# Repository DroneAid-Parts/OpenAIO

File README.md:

# DroneAid OpenAIO

DroneAid OpenAIO is an all-in-one for toothpick-class FPV on 2 to 6 cells: flight controller, 4-in-1 ESC and
ExpressLRS receiver on 25.5 x 25.5 mm mounting, on one PCB. It merges three
boards OpenDrone already makes: OpenFC-Lite-Mini (RP2354A flight controller),
OpenESC-20x20 (AM32 4-in-1) and OpenRX Lite (ELRS receiver). An earlier revision
split it into a Base and a Core hat joined by an LGA; since 2026-10-15 both
are one 8-layer HDI board on the OpenAIO-Whoop stackup.

The KiCad implementation lives in `hardware/`. Use Git for branch state and
manufacturing or test evidence for maturity claims. Layout hand-over:
[research/ROUTING.md](research/ROUTING.md).

## Why

The three-board stack works and OpenDrone already ships all three parts, but on
a toothpick the stack is most of the weight and all of the height. Merging them
removes two connectors, two sets of mounting hardware and a lot of wiring, and
those connectors are where builds fail.

The parts are proven separately, so this is an integration problem rather than
a research one. The only 6S AIO with onboard serial ELRS on the market is
closed and digital-only; an open one with analog OSD and blackbox has a place,
see the market research linked below.

## Specifications

From the design files. Not manufactured yet.

| | |
|---|---|
| Mounting | 25.5 x 25.5 mm, board 35.4 x 35.4 mm |
| Stack | One board: 8-layer HDI 1+6+1, 0.997 mm, 1 oz copper on all layers, ENIG, laser microvias L1-L2 and L7-L8, buried vias L2-L7 (OpenAIO-Whoop stackup). Board rev r3, 2026-10 |
| Input | 2-6S LiPo (6.0-25.2 V), with a low-ESR capacitor of at least 35 V and 220 uF at the battery lead (see Battery lead) |
| Flight controller | RP2354A, BMI270 IMU, DPS368 barometer, analog PIO OSD, microSD blackbox, USB-C |
| ESC | 4x AM32, AT32F421 + NSG2065Q per channel like the OpenESC boards |
| Receiver | ExpressLRS 2.4 GHz, ESP32-C3 + SX1281 |
| Assembly | Chosen per release; see production/. LCSC basic parts preferred |

## Pinout

Measured from `hardware/OpenAIO.kicad_pcb` (pad nets)
and the Betaflight target in `research/review-2026-10/firmware/` (`config.h`,
`PINOUT.md` has the full GPIO map). The silkscreen codes below are the ones
printed next to each pad; port names follow `config.h`.

**Orientation.** Forward is the SH-6 (U12) edge of the Base, battery pads at
the rear. Edge names in the Base table are for the top view with the forward
arrow pointing up (the KiCad view turned 180 degrees). An arrow on the Base top (next to the motor map) and on the Core
bottom (B.Cu copper: no silkscreen may sit in the LGA overlap) points forward. This matches `GYRO_1_ALIGN CW180_DEG`; confirm it in
the configurator Setup tab at bring-up.

### FC pads (the former Core top pads; their place on the one board is not decided yet)

| Pad | Silk | Net | Function |
|---|---|---|---|
| J39 | VTX | `/OSD/VIDEO_OUT` | Analog video out (OSD) to the VTX |
| J38 | CAM | `/OSD/VIDEO_IN` | Analog video in from the camera |
| J30, J37 | 5V | `+5V` | 5 V out |
| J42, J52 | 4V5 (`4.5` at J52) | `+4v5` | 4.5 V rail |
| J34, J35, J40, J43, J50, J53 | GND (`G` where short) | `GND` | Ground |
| J26 | SDA | `/Pads/I2C0.SDA` | I2C0 SDA, GPIO4 (external mag; the onboard DPS368 shares the bus at 0x76) |
| J23 | (legend) SCL | `/Pads/I2C0.SCL` | I2C0 SCL, GPIO5 |
| J44 | TX0 | `/Pads/PIOUART0_TX` | Betaflight UART0 TX, GPIO2 |
| J45 | RX0 | `PU0RX` | Betaflight UART0 RX, GPIO3: SBUS from the air unit (also SH-6 pin 6) |
| J49 | (legend) PTX | `UART0_TX` | Betaflight PIOUART0 TX, GPIO0: MSP DisplayPort (also SH-6 pin 3) |
| J48 | (legend) PRX | `UART0_RX` | Betaflight PIOUART0 RX, GPIO1 (also SH-6 pin 4) |
| J54 | (legend) TX1 | `UART1_TX` | UART1 TX, GPIO6, CRSF to the onboard ELRS (service pad) |
| J55 | RX1 | `UART1_RX` | UART1 RX, GPIO7, CRSF from the onboard ELRS; driven by the ESP32, do not drive it |

The net names are the schematic's; `UART0_TX/RX` on the LGA carry the PIO UART
and `PIOUART0_TX`/`PU0RX` the hardware UART0, because Betaflight cannot run
SBUS on a PIO UART (firmware ISSUES I1).

### Base pads

| Pad | Silk | Net | Function |
|---|---|---|---|
| U24.1 | `+` | `/CSA+` | Battery + (6S), through the current shunt |
| U24.2 | `-` | `GND` | Battery - |
| U24.12-14 | M1 (motor map) | `/1A /1B /1C` | Motor 1, ESC1 (Betaflight MOTOR1, GPIO25): right edge, front half |
| U24.15-17 | M2 | `/2A /2B /2C` | Motor 2, ESC2 (MOTOR2, GPIO24): front edge, right half |
| U24.18-20 | M3 | `/3C /3B /3A` | Motor 3, ESC3 (MOTOR3, GPIO23): rear edge, left half |
| U24.21-23 | M4 | `/4C /4B /4A` | Motor 4, ESC4 (MOTOR4, GPIO22): left edge, rear half |
| J15, J16, J24, J25 | 5V | `+5V` | 5 V for the LED strip, one per corner |
| J17, J18, J27, J28 | GND (bottom) | `GND` | Ground, one per corner |
| J20, J21, J31, J32 | LED (`L` at J20) | `LED_STRIP` | WS2812 data, GPIO8 |
| J41 | (legend) 10V | `+10V` | VTX / air-unit power, always on with a battery (U3 EN is tied to +BATT) |
| J51 | (legend) GND | `GND` | VTX ground |
| U12 | DJI | SH-6 | 1 `+10V`, 2 `GND`, 3 PIOUART0 TX, 4 PIOUART0 RX, 5 `GND`, 6 UART0 RX (SBUS) |
| J33 | BZ+ (bottom) | `+5V` | Buzzer + |
| J29 | BZ- (bottom) | `BUZZER-` | Buzzer - (low-side switched) |
| TP9 | BT0 (bottom) | `/RX/BOOT` | ESP32-C3 boot strap (ELRS flashing) |
| TP31 | (legend) SWD | `SWDIO` | RP2354A SWD data |
| TP32 | (legend) SWC | `SWCLK` | RP2354A SWD clock |
| TP1, TP3, TP4, TP6, TP8 | SD1, SD2, SC2, SC3, SC4 (bottom) | ESC n `PA13`/`PA14` | AM32 SWD of ESC n: SDn = SWDIO (PA13), SCn = SWCLK (PA14) |
| TP2, TP5, TP7 | (legend) SC1, SD3, SD4 | ESC n `PA14`/`PA13` | as above |
| USB1 | none | USB-C | USB (DFU and configurator) |
| JP1 | none | RF | ELRS 2.4 GHz antenna connector |

The motor map (M1-M4 around the forward arrow) on the Base top shows which pad
group belongs to which motor. **Pad legend** for the pads with no room for a
label: Core J23 SCL, J54 TX1, J48 PRX, J49 PTX; Base J41 10V, J51 GND, TP31 SWD,
TP32 SWC, TP2 SC1, TP5 SD3, TP7 SD4. Motor phase letters
are not printed: within each motor group the pads carry phases A, B, C (nets
above); swapping any two reverses the motor, so set direction in AM32 or with
Betaflight's motor direction instead of rewiring.

## Battery lead

- No reverse polarity protection: a reversed battery destroys the board.
- Required: a low-ESR capacitor of at least 35 V (50 V preferred) and 220 uF
  or more at the battery pads. The on-board bank is ceramic only, and a
  hot-plugged 6S pack can ring above the 30 V FETs, the 38 V buck and the 42 V
  current-sense amplifier ([INPUT_RANGE.md](research/review-2026-10/INPUT_RANGE.md)).

## Constraints

- 25.5 x 25.5 mm mounting, the toothpick standard.
- Runs stock firmware: Betaflight on the FC, AM32 per ESC channel, ExpressLRS
  on the receiver. No forks.
- Reuses the manufactured circuits of OpenFC-Lite-Mini, OpenESC-20x20 and
  OpenRX where they fit; parts come from the shared library first.
- Assembly from LCSC parts, extended parts kept to a minimum; assembly house
  chosen per release, see production/.
- Do not start from the three schematics stitched together. That was tried,
  and it produced a board that looked finished and was not (recoverable at the
  `pre-reset-2026-08-13` tag). Start from the requirements.

## Prior art

The three designs this merges, all manufactured and flying:

- [OpenFC-Lite-Mini](https://github.com/OpenDrone-hw/OpenFC-Lite-Mini): the RP2354A flight controller
- [OpenESC-20x20](https://github.com/OpenDrone-hw/OpenESC-20x20): the AM32 4-in-1 power stage
- [OpenRX Lite](https://github.com/OpenDrone-hw/OpenRX-Lite): the ELRS receiver

Research so far, reference rather than decisions:

- [Market research](https://app.notion.com/p/3f5fe06764e1818e9158c512edd58138): competing toothpick and whoop AIOs, June 2026
- [Part alternatives](https://app.notion.com/p/3f5fe06764e1819eade0dc5bfbfdff7c): ESC-stage part alternatives, gate driver and FET options, March 2026
- The stitched design reset in August 2026 is in the git history before #9; reference for the thinking, not a design to continue from.

## Design questions

Resolve these only as part of user-requested design work:

- **Thermal.** Four power stages next to an MCU and a radio on 25.5 mm square,
  with no airflow guarantee. What is the continuous current budget on 1 oz
  copper on all eight layers?
- **RF isolation.** A 2.4 GHz receiver next to four switching power stages.
  Antenna placement, ground plane, shield can or not.

## In the line

What pairs with what, and what is available:
[opendrone.be](https://opendrone.be).

## Contributing

KiCad files cannot be merged, so say what you intend to change before you do,
on [Discord](https://discord.gg/v3sWmTcx3R). How everything works:
[CONTRIBUTING.md](CONTRIBUTING.md).

## License

Hardware licensed under [CERN-OHL-S-2.0](https://ohwr.org/cern_ohl_s_v2.txt),
see [LICENSE](LICENSE).

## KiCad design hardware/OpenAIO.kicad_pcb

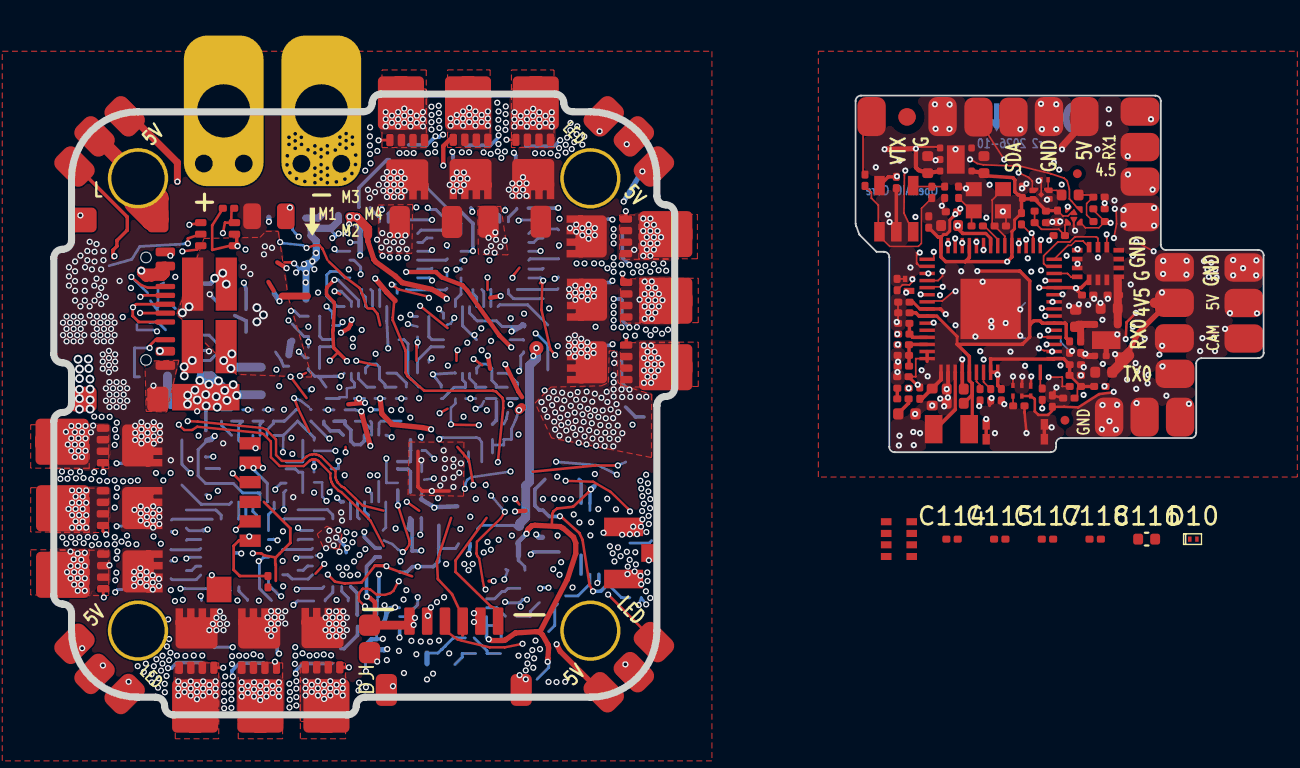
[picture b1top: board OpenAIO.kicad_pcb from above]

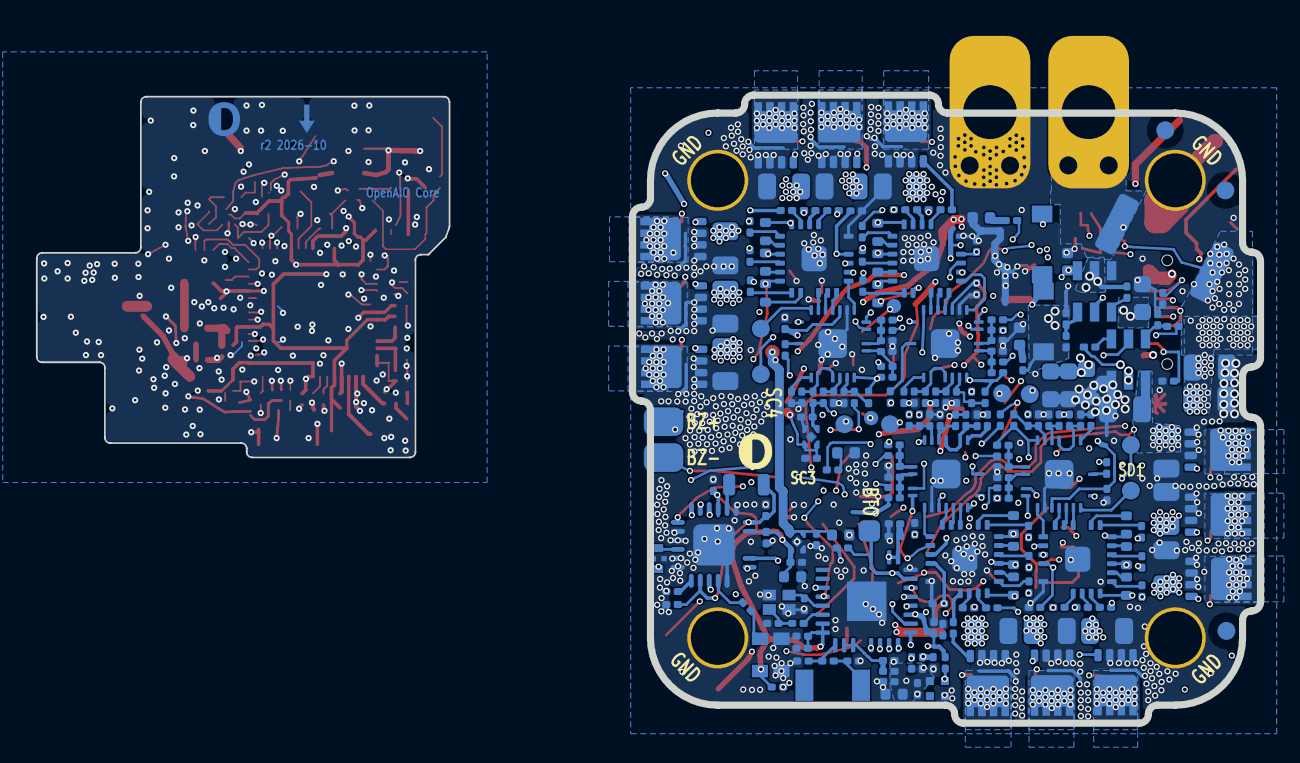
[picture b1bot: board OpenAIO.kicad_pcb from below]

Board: 8 copper layers, 68.2 x 35.0 mm, 362 parts (224 on the bottom side), 239 nets.

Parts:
AE2: 2450AT18A100E; ANT-SMD_L3.2-W1.6
C1, C2, C5, C6, C7, C8, C9, C11, C12, C13, C14, C20, C21, C29, C30, C32, C34, C35, C36, C108, C109, C114, C115, C117, C118: 100n; C_0201_0603Metric
C3, C15, C16, C17, C25, C27: 4.7uF; C_0402_1005Metric
C4, C10: 20p; C_0201_0603Metric
C18, C19, C90, C91, C92, C93, C94, C95, C96, C97, C98, C99, C100, C101, C102, C103: 4.7uF 50v; C_0805_2012Metric
C23, C24, C112, C113: 22uF; C_0603_1608Metric
C26, C28, C33: 1uF; C_0402_1005Metric
C31: 470p; C_0201_0603Metric
C37, C38, C39, C43, C44, C45, C46, C50, C51, C52, C53, C57, C58, C59, C60, C64, C65, C66, C70, C71, C76, C78, C79, C104: 100nF; C_0201_0603Metric
C40, C41, C42, C47, C48, C49, C54, C55, C56, C61, C62, C63: 100nF; C_0402_WIDE
C67, C73, C80: 10nF; C_0201_0603Metric
C68: 470nF; C_0201_0603Metric
C69: 1nF; C_0201_0603Metric
C72, C74: 15pF; C_0201_0603Metric
C75, C82, C88: 10uF; C_0402_1005Metric
C77, C81, C83, C84, C85, C86, C110, C111: 1uF; C_0201_0603Metric
C87, C89: 1.2pF; C_0201_0603Metric
C105, C106: 4.7uF 50v; C_1206_3216Metric
C107, C116: 100nF; C_0402_1005Metric
Card1: TF-021B-H265; TF-SMD_TF-021B-H265
D1: LED_1_Blue; LED_0402_1005Metric
D2, D3: DSK24; SOD-123_L2.8-W1.8-LS3.7-RD
D4, D5, D6, D7: LED_1_Green; LED_0402_1005Metric
D8, D10: SDM02U30LP3-7B; X3-DFN0603-2_L0.6-W0.3-RD
D9: XL-1010RGBC-WS2812B; LED-SMD_4P-L1.0-W1.0-TL_XL-1010RGBC-WS2812B
FID1, FID2, FID3, FID4: Fiducial_1mm_Mask2mm
FID5, FID6: Fiducial_1mm_Mask2mm; Fiducial_0.5mm_Mask1mm
FL1: 2450FM07D0034T; FILTER-SMD_4P-L1.0-W0.5-L
J15, J16, J24, J25, J30, J37: 5V; small_pad
J17, J18, J27, J28, J34, J35, J40, J43, J50, J53: GND; small_pad
J20, J21, J31, J32: LED; small_pad
J23: SCL; small_pad
J26: SDA; small_pad
J29: BUZ-; small_pad
J33: BUZ+; small_pad
J38: CAM; small_pad
J39: VTX; small_pad
J41: 10V; SolderPad_1.2x1.2mm
J42, J52: 4V5; small_pad
J44: PIO_TX0; small_pad
J45: PIO_RX0; small_pad
J48: RX0; small_pad
J49: TX0; small_pad
J51: GND; SolderPad_1.2x1.2mm
J54: TX1; small_pad
J55: RX1; small_pad
JP1: U.FL-R-SMT-1(80); RF-SMD_FRF05002-JSS103M
L1: AOTA-B201610S3R3-101-T; IND-SMD_L2.0-W1.6_AOTA-B201610S3R3-101-T
L2, L3: XRTC303020D4R7MBCA; IND-SMD_L3.0-W3.0_AFE303020S
L4: 15uH; L_0805_2012Metric
L5: 24nH; L_0201_0603Metric
L6: 2.0nH; L_0201_0603Metric
L7: 2.5nH; L_0201_0603Metric
OSC1: OW7EL89CENUNFAYLC-52M; OSC-SMD_4P-L2.0-W1.6-BL_TXC_7Z
Q1: AP1606; DFN-3L_L1.0-W0.6-P0.65-BR
Q3, Q4, Q5, Q6, Q7, Q8, Q9, Q10, Q11, Q12, Q13, Q14, Q15, Q16, Q17, Q18, Q19, Q20, Q21, Q22, Q23, Q24, Q25, Q26: DOY180N03T; DOY180N03T_TDFN3333-8
R1, R13, R17, R19: 100k; R_0201_0603Metric
R2, R25, R34, R37, R38, R45, R47, R48, R50, R51, R53, R56, R57, R64, R66, R67, R69, R70, R72, R75, R76, R83, R85, R86, R88, R89, R91, R94, R95, R102, R104, R105, R107, R108, R110, R111, R112, R113, R114: 10k; R_0201_0603Metric
R3, R4, R11, R12: 5.1k; R_0201_0603Metric
R5, R6, R7, R46, R49, R52, R65, R68, R71, R84, R87, R90, R103, R106, R109: 1k; R_0201_0603Metric
R8, R9, R10: 30R; R_0201_0603Metric
R15, R16, R26, R33: 75R; R_0201_0603Metric
R18, R23: 6.49k; R_0201_0603Metric
R20: 13.7k; R_0201_0603Metric
R21: 7.5k; R_0201_0603Metric
R22: 2.4k; R_0201_0603Metric
R24, R31, R32: 510R; R_0201_0603Metric
R27: 3.9k; R_0201_0603Metric
R28: 12k; R_0201_0603Metric
R29: 1.4k; R_0201_0603Metric
R30: 680R; R_0201_0603Metric
R35, R36, R41, R42, R43, R44, R54, R55, R60, R61, R62, R63, R73, R74, R79, R80, R81, R82, R92, R93, R98, R99, R100, R101: 15R; R_0201_0603Metric
R39, R58, R77, R96: 220R; R_0201_0603Metric
R40, R59, R78, R97: 10R; R_0201_0603Metric
R115: 200R; R_0201_0603Metric
Rsense2: 0.2mR; R_2512_6332Metric
TP1, TP2, TP3, TP4, TP5, TP6, TP7, TP8: TestPoint; TestPoint_Pad_D1.0mm
TP9: BOOT; SolderPad_1.2x2.0mm
TP31: SWDIO; TestPoint_Pad_D0.8mm
TP32: SWCLK; TestPoint_Pad_D0.8mm
U1: TS2306A 240GF MSM 9_C2976675; SW-SMD_4P-L3.0-W2.0-P0.85-LS3.5
U2: RP2354A; QFN-60_L7.0-W7.0-P0.40-TL-EP3.4
U3, U4: LMR51430YFDDCR; SOT-23-6_L2.9-W1.6-P0.95-LS2.9-BL
U6: LP5912-1.8DRVR; WSON-6-1EP_2x2mm_P0.65mm_EP1x1.6mm_ThermalVias
U7: LP5912-3.3DRVR; WSON-6-1EP_2x2mm_P0.65mm_EP1x1.6mm
U8: BMI270; LGA-14_L3.0-W2.5-P0.50-BR
U9: SN74LVC1G3157DTBR; X2SON-6_L1.0-W0.8-BL
U10: COS8051SOT; SOT-23-5_L3.0-W1.7-P0.95-LS2.8-BR
U11: TLV7031DPWR; X2SON-4_L0.8-W0.8-P0.48-TL-A
U12: SM06B-SRSS-TB(LF)(SN); CONN-SMD_SM06B-SRSS-TB-LF-SN
U13, U15, U17, U19: AT32F421G8U7; QFN-28_L4.0-W4.0-P0.40-TL-EP2.4
U14, U16, U18, U20: NSG2065Q; QFN-24_L4.0-W4.0-P0.50-TL-EP2.8
U21: SX1281IMLTRT; QFN-24_L4.0-W4.0-P0.50-TL-EP2.6
U22: ESP32-C3FH4; QFN-32-1EP_5x5mm_P0.5mm_EP3.7x3.7mm
U23, U27: TLV75533PDQNR; X2SON-4_L1.0-W1.0-P0.65-TL-EP
U24: AIO_outline
U25: INA186A3IDCKR; SOT-363_SC-70-6
U26: TXU0101DRYR; SON-6_L1.5-W1.0-P0.50-TL
U28: DPS368XTSA1; LGA-8_L2.5-W2.0-P0.65-TR_DPS368
USB1: TYPE-C 16P QTWT; USB-TYPE-C-SMD_TYPE-C-16P-QTWT
X1: XTM25012000JT00351001; CRYSTAL-SMD_4P-L2.5-W2.0-BL-A
X2: CJ17-400001010B20; CRYSTAL-SMD_4P-L1.6-W1.2-BL

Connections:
+1.1V: C1.1, C3.1, C5.1, C16.1, L1.1, U2.6 (DVDD), U2.23 (DVDD), U2.39 (DVDD), U2.50 (VREG_FB)
+1.8V_GYRO: C27.1, C29.1, U6.1 (OUT), U8.8 (Vdd)
+3.3V: C6.1, C7.1, C8.1, C11.1, C12.1, C13.1, C14.1, C15.1, C28.1, C30.1, C32.1, C34.1, C35.1, C36.1, C108.1, C114.1, C115.1, C117.1, C118.1, Card1.4 (VDD), R10.1, R11.1, R12.1, R25.2, R28.2, R34.1, U2.1 (IOVDD), U2.11 (IOVDD), U2.20 (IOVDD), U2.26 (RUN), U2.30 (IOVDD), U2.38 (IOVDD), U2.44 (ADC_AVDD), U2.45 (IOVDD), U2.49 (VREG_VIN), U2.53 (USB_OTP_VDD), U2.54 (QSPI_IOVDD), U7.1 (OUT), U8.2 (SDx/AH1/Qvar1), U8.3 (SCx/AH2/Qvar2), U8.5 (Vdd_IO), U9.5 (VCC), U10.5 (+VS), U11.2 (VCC), U26.1 (VCCA), U28.2 (CSB), U28.6 (VDDIO), U28.8 (VDD)
+3V3: C65.1, C66.1, C70.1, C71.1, C75.1, C76.1, C78.1, C79.1, C80.1, C81.1, C83.1, C86.1, C88.1, C104.1, L6.2, OSC1.4 (VDD), R24.1, R111.1, R112.1, R113.1, R114.2, U21.11 (VBAT_IO), U21.15 (VBAT), U22.11 (VDD3P3_RTC), U22.17 (VDD3P3_CPU), U22.18 (VDD_SPI), U22.31 (VDDA), U22.32 (VDDA), U23.1 (OUT), U25.3 (VS)
+3V3_ESC: C39.1, C46.1, C53.1, C60.1, C111.1, R37.2, R40.2, R56.2, R59.2, R75.2, R78.2, R94.2, R97.2, U13.17 (VDD), U15.17 (VDD), U17.17 (VDD), U19.17 (VDD), U27.1 (OUT)
+4v5: C25.1, C26.1, C82.1, C85.1, D2.1 (K), D3.1 (K), D9.2 (VDD), J42.1 (Pin_1_1), J52.1 (Pin_1_1), R23.1, U6.4 (EN), U6.6 (IN), U7.4 (EN), U7.6 (IN), U23.3 (EN), U23.4 (IN)
+5V: C24.1, C109.1, C110.1, D2.2 (A), D10.1 (C), J15.1 (Pin_1_1), J16.1 (Pin_1_1), J24.1 (Pin_1_1), J25.1 (Pin_1_1), J30.1 (Pin_1_1), J33.1 (Pin_1_1), J37.1 (Pin_1_1), L3.2, R19.2, R22.1, U26.5 (OE), U26.6 (VCCB), U27.3 (EN), U27.4 (IN)
+5V_USB: D3.2 (A), USB1.A4 (VBUS), USB1.A9 (VBUS)
+10V: C23.1, C43.1, C50.1, C57.1, C64.1, C112.1, C113.1, J41.1 (Pin_1_1), L2.2, R17.2, R21.1, U12.1, U14.4 (VCC), U16.4 (VCC), U18.4 (VCC), U20.4 (VCC)
+BATT: C18.1, C19.1, C90.1, C91.1, C92.1, C93.1, C94.1, C95.1, C96.1, C97.1, C98.1, C99.1, C100.1, C101.1, C102.1, C103.1, C105.1, C106.1, C107.1, C116.1, Q3.3 (D), Q5.3 (D), Q7.3 (D), Q9.3 (D), Q11.3 (D), Q13.3 (D), Q15.3 (D), Q17.3 (D), Q19.3 (D), Q21.3 (D), Q23.3 (D), Q25.3 (D), R1.2, Rsense2.2, U3.3 (VIN), U3.5 (EN), U4.3 (VIN), U4.5 (EN), U25.5 (-IN)
/1A: C40.1, Q3.1 (S), Q4.3 (D), R47.1, U14.18 (VS1), U24.12 (4A)
/1B: C41.1, Q5.1 (S), Q6.3 (D), R50.1, U14.15 (VS2), U24.13 (4B)
/1C: C42.1, Q7.1 (S), Q8.3 (D), R53.1, U14.12 (VS3), U24.14 (4C)
/2A: C47.1, Q9.1 (S), Q10.3 (D), R66.1, U16.18 (VS1), U24.15 (3B)
/2B: C48.1, Q11.1 (S), Q12.3 (D), R69.1, U16.15 (VS2), U24.16 (3C)
/2C: C49.1, Q13.1 (S), Q14.3 (D), R72.1, U16.12 (VS3), U24.17 (3A)
/3A: C54.1, Q15.1 (S), Q16.3 (D), R85.1, U18.18 (VS1), U24.20 (2B)
/3B: C55.1, Q17.1 (S), Q18.3 (D), R88.1, U18.15 (VS2), U24.19 (2C)
/3C: C56.1, Q19.1 (S), Q20.3 (D), R91.1, U18.12 (VS3), U24.18 (2A)
/4A: C61.1, Q21.1 (S), Q22.3 (D), R104.1, U20.18 (VS1), U24.23 (1A)
/4B: C62.1, Q23.1 (S), Q24.3 (D), R107.1, U20.15 (VS2), U24.22 (1B)
/4C: C63.1, Q25.1 (S), Q26.3 (D), R110.1, U20.12 (VS3), U24.21 (1C)
/CSA+: Rsense2.1, U24.1 (VBAT), U25.4 (+IN)
/ESC1/AH: U13.20 (PA10), U14.22 (HIN1)
/ESC1/AL: U13.15 (PB1), U14.1 (LIN1)
/ESC1/BH: U13.19 (PA9), U14.23 (HIN2)
/ESC1/BL: U13.14 (PB0), U14.2 (LIN2)
/ESC1/CH: U13.18 (PA8), U14.24 (HIN3)
/ESC1/CL: U13.13 (PA7), U14.3 (LIN3)
/ESC1/FBA: R45.1, R46.2, R47.2, U13.6 (PA0)
/ESC1/FBB: R48.2, R49.2, R50.2, U13.10 (PA4)
/ESC1/FBC: R51.2, R52.2, R53.2, U13.11 (PA5)
/ESC1/FBCOMMON: R45.2, R48.1, R51.1, U13.7 (PA1)
/ESC1/GHA: R35.1, U14.19 (HO1)
/ESC1/GHB: R41.1, U14.16 (HO2)
/ESC1/GHC: R43.1, U14.13 (HO3)
/ESC1/GLA: R36.1, U14.11 (LO1)
/ESC1/GLB: R42.1, U14.10 (LO2)
/ESC1/GLC: R44.1, U14.9 (LO3)
/ESC1/vdda: C38.1, R40.1, U13.5 (VDDA)
/ESC2/AH: U15.20 (PA10), U16.22 (HIN1)
/ESC2/AL: U15.15 (PB1), U16.1 (LIN1)
/ESC2/BH: U15.19 (PA9), U16.23 (HIN2)
/ESC2/BL: U15.14 (PB0), U16.2 (LIN2)
/ESC2/CH: U15.18 (PA8), U16.24 (HIN3)
/ESC2/CL: U15.13 (PA7), U16.3 (LIN3)
/ESC2/FBA: R64.1, R65.2, R66.2, U15.6 (PA0)
/ESC2/FBB: R67.2, R68.2, R69.2, U15.10 (PA4)
/ESC2/FBC: R70.2, R71.2, R72.2, U15.11 (PA5)
/ESC2/FBCOMMON: R64.2, R67.1, R70.1, U15.7 (PA1)
/ESC2/GHA: R54.1, U16.19 (HO1)
/ESC2/GHB: R60.1, U16.16 (HO2)
/ESC2/GHC: R62.1, U16.13 (HO3)
/ESC2/GLA: R55.1, U16.11 (LO1)
/ESC2/GLB: R61.1, U16.10 (LO2)
/ESC2/GLC: R63.1, U16.9 (LO3)
/ESC2/vdda: C45.1, R59.1, U15.5 (VDDA)
/ESC3/AH: U17.20 (PA10), U18.22 (HIN1)
/ESC3/AL: U17.15 (PB1), U18.1 (LIN1)
/ESC3/BH: U17.19 (PA9), U18.23 (HIN2)
/ESC3/BL: U17.14 (PB0), U18.2 (LIN2)
/ESC3/CH: U17.18 (PA8), U18.24 (HIN3)
/ESC3/CL: U17.13 (PA7), U18.3 (LIN3)
/ESC3/FBA: R83.1, R84.2, R85.2, U17.6 (PA0)
/ESC3/FBB: R86.2, R87.2, R88.2, U17.10 (PA4)
/ESC3/FBC: R89.2, R90.2, R91.2, U17.11 (PA5)
/ESC3/FBCOMMON: R83.2, R86.1, R89.1, U17.7 (PA1)
/ESC3/GHA: R73.1, U18.19 (HO1)
/ESC3/GHB: R79.1, U18.16 (HO2)
/ESC3/GHC: R81.1, U18.13 (HO3)
/ESC3/GLA: R74.1, U18.11 (LO1)
/ESC3/GLB: R80.1, U18.10 (LO2)
/ESC3/GLC: R82.1, U18.9 (LO3)
/ESC3/vdda: C52.1, R78.1, U17.5 (VDDA)
/ESC4/AH: U19.20 (PA10), U20.22 (HIN1)
/ESC4/AL: U19.15 (PB1), U20.1 (LIN1)
/ESC4/BH: U19.19 (PA9), U20.23 (HIN2)
/ESC4/BL: U19.14 (PB0), U20.2 (LIN2)
/ESC4/CH: U19.18 (PA8), U20.24 (HIN3)
/ESC4/CL: U19.13 (PA7), U20.3 (LIN3)
/ESC4/FBA: R102.1, R103.2, R104.2, U19.6 (PA0)
/ESC4/FBB: R105.2, R106.2, R107.2, U19.10 (PA4)
/ESC4/FBC: R108.2, R109.2, R110.2, U19.11 (PA5)
/ESC4/FBCOMMON: R102.2, R105.1, R108.1, U19.7 (PA1)
/ESC4/GHA: R92.1, U20.19 (HO1)
/ESC4/GHB: R98.1, U20.16 (HO2)
/ESC4/GHC: R100.1, U20.13 (HO3)
/ESC4/GLA: R93.1, U20.11 (LO1)
/ESC4/GLB: R99.1, U20.10 (LO2)
/ESC4/GLC: R101.1, U20.9 (LO3)
/ESC4/vdda: C59.1, R97.1, U19.5 (VDDA)
/IMU/CS: R25.1, U2.17 (GPIO13), U8.12 (CS)
/IMU/GYRO_INT: U2.13 (GPIO9), U8.4 (INT1)
/IMU/SPI1.MISO: U2.16 (GPIO12), U8.1 (SDO/SA0)
/IMU/SPI1.MOSI: U2.15 (GPIO11), U8.14 (SDA)
/IMU/SPI1.SCK: U2.14 (GPIO10), U8.13 (SCL)
/OSD/OSD_EN: U2.19 (GPIO15), U9.6 (S)
/OSD/OSD_LVL: R27.2, R28.1, R29.2, U9.1 (B2)
/OSD/OSD_SYNC: U2.27 (GPIO16), U11.1 (OUT)
/OSD/OSD_W: R27.1, U2.18 (GPIO14)
/OSD/VIDEO_IN: J38.1 (Pin_1_1), R26.1, R30.2, U9.3 (B1)
/OSD/VIDEO_OUT: J39.1 (Pin_1_1), R33.2
/OSD/VID_DC: C33.2, D8.1 (C), U11.4 (IN+)
/OSD/VID_FILT: C31.1, C33.1, R30.1
/Pads/I2C0.SCL: J23.1 (Pin_1_1), R11.2, U2.8 (GPIO5), U28.4 (SCK)
/Pads/I2C0.SDA: J26.1 (Pin_1_1), R12.2, U2.7 (GPIO4), U28.3 (SDI)
/Pads/PIOUART0_TX: J44.1 (Pin_1_1), U2.4 (GPIO2)
/Power/1.8V_PG: D7.2 (A), R23.2, U6.3 (PG)
/RP2354A/ADC_VBAT: C2.2, R1.1, R2.2, U2.43 (GPIO29_ADC3)
/RP2354A/BEEPER: Q1.1 (G), R13.2, U2.28 (GPIO17)
/RP2354A/ESC_CURR: C9.1, R5.2, U2.42 (GPIO28_ADC2)
/RP2354A/LED0: R15.1, U2.40 (GPIO26_ADC0)
/RP2354A/LED_STRIP_L: U2.12 (GPIO8), U26.3 (A)
/RP2354A/XIN: C4.2, U2.21 (XIN), X1.1
/RP2354A/XOUT: R6.1, U2.22 (XOUT)
/RX/BOOT: R113.2, TP9.1 (1_1), U22.15 (GPIO9)
/RX/BUSY: U21.7 (BUSY), U22.8 (GPIO3)
/RX/CHIP_EN: C84.1, R114.1, U22.7 (CHIP_EN)
/RX/DIO1: U21.8 (DIO1), U22.5 (XTAL_32K_N)
/RX/LED: D9.4 (DIN), R112.2, U22.14 (GPIO8)
/RX/MISO: U21.16 (MISO_TX), U22.10 (MTDI)
/RX/MOSI: U21.17 (MOSI_RX), U22.9 (MTMS)
/RX/NSS: U21.19 (NSS_CTS), U22.13 (MTDO)
/RX/RST: R111.2, U21.3 (NRESET), U22.6 (GPIO2)
/RX/SCK: U21.18 (SCK_RTSN), U22.12 (MTCK)
/RX/WIFI: AE2.1, C89.1, L7.1
/RX/XTAL_N: C74.1, U22.29 (XTAL_N), X2.3
/RX/XTAL_P: L5.2, U22.30 (XTAL_P)
BUZZER-: D10.2 (A), J29.1 (Pin_1_1), Q1.3 (D)
CURR: R5.1, U25.6 (OUT)
GND: C1.2, C2.1, C3.2, C4.1, C5.2, C6.2, C7.2, C8.2, C9.2, C10.1, C11.2, C12.2, C13.2, C14.2, C15.2, C16.2, C17.2, C18.2, C19.2, C23.2, C24.2, C25.2, C26.2, C27.2, C28.2, C29.2, C30.2, C31.2, C32.2, C34.2, C35.2, C36.2, C37.2, C38.2, C39.2, C43.2, C44.2, C45.2, C46.2, C50.2, C51.2, C52.2, C53.2, C57.2, C58.2, C59.2, C60.2, C64.2, C65.2, C66.2, C67.1, C68.1, C70.2, C71.2, C72.2, C73.2, C74.2, C75.2, C76.2, C77.2, C78.2, C79.2, C80.2, C81.2, C82.2, C83.2, C84.2, C85.2, C86.2, C87.2, C88.2, C89.2, C90.2, C91.2, C92.2, C93.2, C94.2, C95.2, C96.2, C97.2, C98.2, C99.2, C100.2, C101.2, C102.2, C103.2, C104.2, C105.2, C106.2, C107.2, C108.2, C109.2, C110.2, C111.2, C112.2, C113.2, C114.2, C115.2, C116.2, C117.2, C118.2, Card1.6 (VSS), Card1.9, Card1.10, D1.1 (K), D4.1 (K), D5.1 (K), D6.1 (K), D7.1 (K), D8.2 (A), D9.3 (GND), FL1.2 (GND), FL1.4 (GND), J17.1 (Pin_1_1), J18.1 (Pin_1_1), J27.1 (Pin_1_1), J28.1 (Pin_1_1), J34.1 (Pin_1_1), J35.1 (Pin_1_1), J40.1 (Pin_1_1), J43.1 (Pin_1_1), J50.1 (Pin_1_1), J51.1 (Pin_1_1), J53.1 (Pin_1_1), JP1.2 (GND), JP1.3 (GND), OSC1.1 (GND), OSC1.2 (GND), Q1.2 (S), Q4.1 (S), Q6.1 (S), Q8.1 (S), Q10.1 (S), Q12.1 (S), Q14.1 (S), Q16.1 (S), Q18.1 (S), Q20.1 (S), Q22.1 (S), Q24.1 (S), Q26.1 (S), R2.1, R3.1, R4.1, R13.1, R18.2, R20.2, R26.2, R29.1, R31.2, R38.2, R46.1, R49.1, R52.1, R57.2, R65.1, R68.1, R71.1, R76.2, R84.1, R87.1, R90.1, R95.2, R103.1, R106.1, R109.1, U1.1, U2.47 (VREG_PGND), U2.61 (EP), U3.1 (GND), U4.1 (GND), U6.5 (GND), U6.7 (EP), U7.3 (PG), U7.5 (GND), U7.7 (EP), U8.6 (GND), U8.7 (GND), U9.2 (GND), U10.2 (-VS), U11.3 (IN-), U11.5 (VEE), U12.2, U12.5, U12.7, U12.8, U13.16 (VSS), U13.29 (VSS), U14.6 (COM), U14.25 (COM), U15.16 (VSS), U15.29 (VSS), U16.6 (COM), U16.25 (COM), U17.16 (VSS), U17.29 (VSS), U18.6 (COM), U18.25 (COM), U19.16 (VSS), U19.29 (VSS), U20.6 (COM), U20.25 (COM), U21.5 (GND), U21.13 (GND), U21.20 (GND), U21.21 (GND), U21.23 (GND), U21.24 (GND), U21.25 (EP), U22.16 (GPIO10), U22.33 (GND), U23.2 (GND), U23.5 (EP), U24.2 (BATGND), U24.11 (Hole), U25.1 (REF), U25.2 (GND), U26.2 (GND), U27.2 (GND), U27.5 (EP), U28.1 (GND), U28.5 (SDO), U28.7 (GND), USB1.0 (EH), USB1.A1 (GND), USB1.A12 (GND), X1.2 (GND), X1.4 (GND), X2.2 (GND), X2.4 (GND)
LED_STRIP: J20.1 (Pin_1_1), J21.1 (Pin_1_1), J31.1 (Pin_1_1), J32.1 (Pin_1_1), R115.2
MOTOR1: R39.1, U2.37 (GPIO25)
MOTOR2: R58.1, U2.36 (GPIO24)
MOTOR3: R77.1, U2.35 (GPIO23)
MOTOR4: R96.1, U2.34 (GPIO22)
unnamed: C10.2, R6.2, X1.3
unnamed: C72.1, L5.1, X2.1
unnamed: C77.1, L6.1, U22.2 (VDD3P3), U22.3 (VDD3P3)
unnamed: D1.2 (A), R16.2
unnamed: D4.2 (A), R21.2
unnamed: D5.2 (A), R22.2
unnamed: D6.2 (A), R24.2
unnamed: FL1.1 (IN), U21.22 (RFIO)
unnamed: FL1.3 (OUT), JP1.1 (SIG)
unnamed: C69.1, OSC1.3 (Out_Put)
unnamed: Q3.2 (G), R35.2
unnamed: Q4.2 (G), R36.2
unnamed: Q5.2 (G), R41.2
unnamed: Q6.2 (G), R42.2
unnamed: Q7.2 (G), R43.2
unnamed: Q8.2 (G), R44.2
unnamed: Q9.2 (G), R54.2
unnamed: Q10.2 (G), R55.2
unnamed: Q11.2 (G), R60.2
unnamed: Q12.2 (G), R61.2
unnamed: Q13.2 (G), R62.2
unnamed: Q14.2 (G), R63.2
unnamed: Q15.2 (G), R73.2
unnamed: Q16.2 (G), R74.2
unnamed: Q17.2 (G), R79.2
unnamed: Q18.2 (G), R80.2
unnamed: Q19.2 (G), R81.2
unnamed: Q20.2 (G), R82.2
unnamed: Q21.2 (G), R92.2
unnamed: Q22.2 (G), R93.2
unnamed: Q23.2 (G), R98.2
unnamed: Q24.2 (G), R99.2
unnamed: Q25.2 (G), R100.2
unnamed: Q26.2 (G), R101.2
unnamed: R7.1, U1.2
unnamed: R15.2, R16.1
unnamed: R7.2, U2.60 (QSPI_SS)
unnamed: R8.2, U2.51 (USB_DM)
unnamed: R9.1, U2.52 (USB_DP)
unnamed: C17.1, R10.2, U2.46 (VREG_AVDD)
unnamed: L1.2, U2.48 (VREG_LX)
unnamed: C20.2, U3.6 (CB)
unnamed: R17.1, R18.1, U3.4 (FB)
unnamed: C20.1, L2.1, U3.2 (SW)
unnamed: C21.2, U4.6 (CB)
unnamed: R19.1, R20.1, U4.4 (FB)
unnamed: C21.1, L3.1, U4.2 (SW)
unnamed: U9.4 (A), U10.3 (IN+)
unnamed: R31.1, R32.1, U10.4 (IN-)
unnamed: R32.2, R33.1, U10.1 (OUT)
unnamed: R38.1, U13.1 (BOOT0)
unnamed: C37.1, R37.1, U13.4 (NRST)
unnamed: TP1.1 (1_1), U13.21 (PA13)
unnamed: TP2.1 (1_1), U13.22 (PA14)
unnamed: R39.2, U13.25 (PB4)
unnamed: C40.2, U14.20 (VB1)
unnamed: C41.2, U14.17 (VB2)
unnamed: C42.2, U14.14 (VB3)
unnamed: R57.1, U15.1 (BOOT0)
unnamed: C44.1, R56.1, U15.4 (NRST)
unnamed: TP3.1 (1_1), U15.21 (PA13)
unnamed: TP4.1 (1_1), U15.22 (PA14)
unnamed: R58.2, U15.25 (PB4)
unnamed: C47.2, U16.20 (VB1)
unnamed: C48.2, U16.17 (VB2)
unnamed: C49.2, U16.14 (VB3)
unnamed: R76.1, U17.1 (BOOT0)
unnamed: C51.1, R75.1, U17.4 (NRST)
unnamed: TP5.1 (1_1), U17.21 (PA13)
unnamed: TP6.1 (1_1), U17.22 (PA14)
unnamed: R77.2, U17.25 (PB4)
unnamed: C54.2, U18.20 (VB1)
unnamed: C55.2, U18.17 (VB2)
unnamed: C56.2, U18.14 (VB3)
unnamed: R95.1, U19.1 (BOOT0)
unnamed: C58.1, R94.1, U19.4 (NRST)
unnamed: TP7.1 (1_1), U19.21 (PA13)
unnamed: TP8.1 (1_1), U19.22 (PA14)
unnamed: R96.2, U19.25 (PB4)
unnamed: C61.2, U20.20 (VB1)
unnamed: C62.2, U20.17 (VB2)
unnamed: C63.2, U20.14 (VB3)
unnamed: C67.2, C68.2, L4.1, U21.2 (VDD_IN), U21.12 (DCC_FB)
unnamed: L4.2, U21.14 (DCC_SW)
unnamed: C73.1, U21.1 (VR_PA)
unnamed: C69.2, U21.4 (XTA)
unnamed: C87.1, L7.2, U22.1 (LNA_IN)
unnamed: R115.1, U26.4 (BY)
unnamed: R3.2, USB1.A5 (CC1)
unnamed: R4.2, USB1.B5 (CC2)
PU0RX: J45.1 (Pin_1_1), U2.5 (GPIO3), U12.6
SD_CS: Card1.2 (CD/DAT3), R34.2, U2.33 (GPIO21)
SPI0.MISO: Card1.7 (DAT0), U2.32 (GPIO20)
SPI0.MOSI: Card1.3 (CMD), U2.31 (GPIO19)
SPI0.SCK: Card1.5 (CLX), U2.29 (GPIO18)
SWCLK: TP32.1 (1_1), U2.24 (SWCLK)
SWDIO: TP31.1 (1_1), U2.25 (SWDIO)
UART0_RX: J48.1 (Pin_1_1), U2.3 (GPIO1), U12.4
UART0_TX: J49.1 (Pin_1_1), U2.2 (GPIO0), U12.3
UART1_RX: J55.1 (Pin_1_1), U2.10 (GPIO7), U22.28 (U0TXD)
UART1_TX: J54.1 (Pin_1_1), U2.9 (GPIO6), U22.27 (U0RXD)
USB_D+: R9.2, USB1.A6 (DP1), USB1.B6 (DP2)
USB_D-: R8.1, USB1.A7 (DN1), USB1.B7 (DN2)
